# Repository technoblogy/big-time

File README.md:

# Big Time
A giant digital clock featuring four large LED displays.
For more information see: http://www.technoblogy.com/show?2WTD.

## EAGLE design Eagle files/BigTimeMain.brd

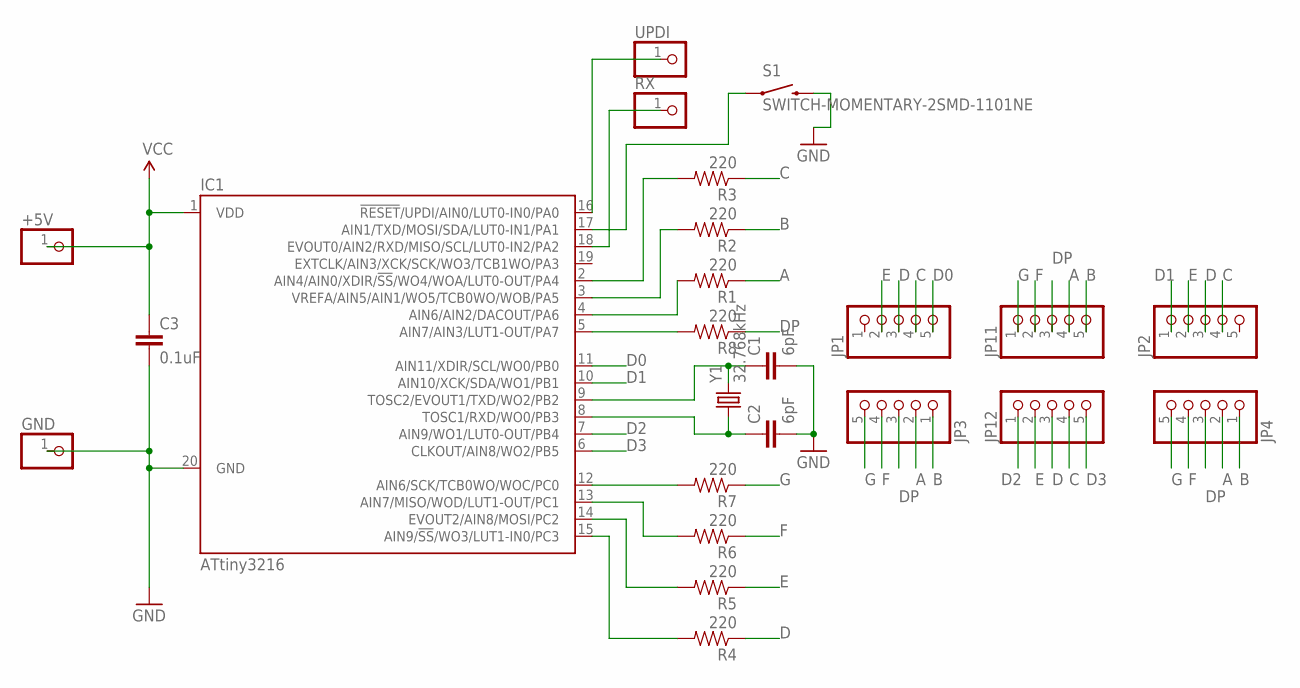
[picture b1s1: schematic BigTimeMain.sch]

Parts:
+5V: PINHD-1X1; 1X01
C1, C2: 6pF; 0805
C3: 0.1uF; 0805
GND: PINHD-1X1; 1X01
IC1: ATtiny3216; SOIC300
JP1, JP2, JP3, JP4, JP11, JP12: HEADER-1X576MIL; 1X05_ROUND_76
R1, R2, R3, R4, R5, R6, R7, R8: 220; 0805
RX: PINHD-1X1; 1X01
S1: SWITCH-MOMENTARY-2SMD-1101NE; TACTILE-SWITCH-1101NE
UPDI: PINHD-1X1; 1X01
Y1: 32.768kHz; CRYSTAL-SMD-3.2X1.5MM

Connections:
A: JP3.2, JP4.2, JP11.4, R1.1
B: JP3.1, JP4.1, JP11.5, R2.1
C: JP1.4, JP2.4, JP12.4, R3.1
D: JP1.3, JP2.3, JP12.3, R4.1
D0: IC1.11 (AIN11/XDIR/SCL/WO0/PB0), JP1.5
D1: IC1.10 (AIN10/XCK/SDA/WO1/PB1), JP2.1
D2: IC1.7 (AIN9/WO1/LUT0-OUT/PB4), JP12.1
D3: IC1.6 (CLKOUT/AIN8/WO2/PB5), JP12.5
DP: JP3.3, JP4.3, JP11.3, R8.1
E: JP1.2, JP2.2, JP12.2, R5.1
F: JP3.4, JP4.4, JP11.2, R6.1
G: JP3.5, JP4.5, JP11.1, R7.1
GND: C1.2, C2.2, C3.2, GND.1, IC1.20 (GND), S1.2
unnamed: C1.1, IC1.9 (TOSC2/EVOUT1/TXD/WO2/PB2), Y1.P$2 (2)
unnamed: C2.1, IC1.8 (TOSC1/RXD/WO0/PB3), Y1.P$1 (1)
unnamed: IC1.16 (!RESET!/UPDI/AIN0/LUT0-IN0/PA0), UPDI.1
unnamed: IC1.4 (AIN6/AIN2/DACOUT/PA6), R1.2
unnamed: IC1.3 (VREFA/AIN5/AIN1/WO5/TCB0WO/WOB/PA5), R2.2
unnamed: IC1.2 (AIN4/AIN0/XDIR/!SS!/WO4/WOA/LUT0-OUT/PA4), R3.2
unnamed: IC1.15 (AIN9/!SS!/WO3/LUT1-IN0/PC3), R4.2
unnamed: IC1.14 (EVOUT2/AIN8/MOSI/PC2), R5.2
unnamed: IC1.18 (EVOUT0/AIN2/RXD/MISO/SCL/LUT0-IN2/PA2), RX.1
unnamed: IC1.13 (AIN7/MISO/WOD/LUT1-OUT/PC1), R6.2
unnamed: IC1.12 (AIN6/SCK/TCB0WO/WOC/PC0), R7.2
unnamed: IC1.5 (AIN7/AIN3/LUT1-OUT/PA7), R8.2
unnamed: IC1.17 (AIN1/TXD/MOSI/SDA/LUT0-IN1/PA1), S1.1
VCC: +5V.1, C3.1, IC1.1 (VDD)

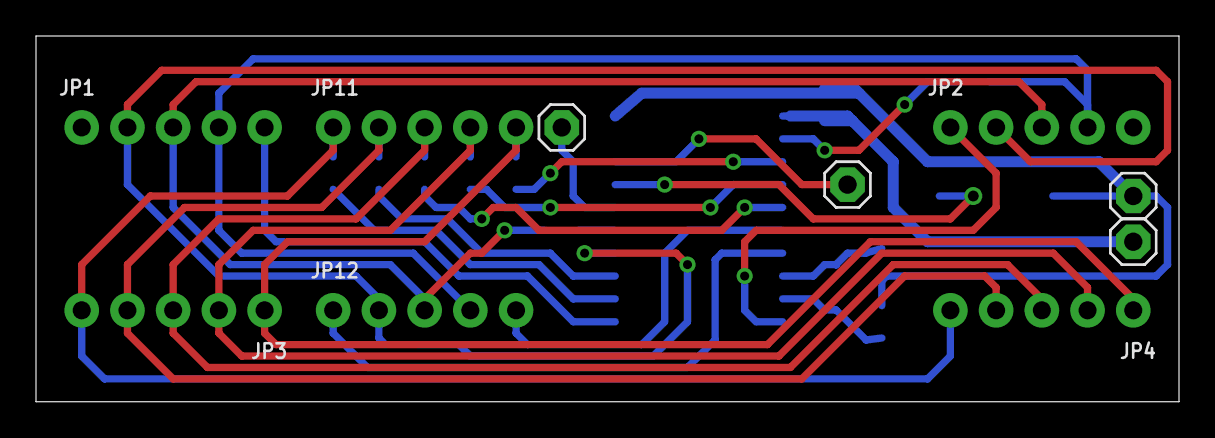
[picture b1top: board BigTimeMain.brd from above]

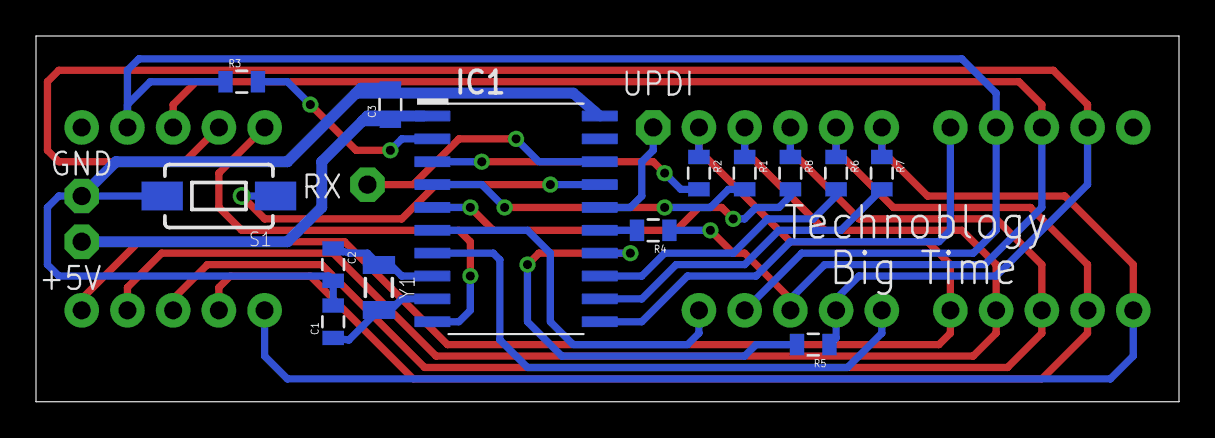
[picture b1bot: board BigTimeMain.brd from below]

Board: 2 copper layers, 63.5 x 20.3 mm, 24 parts (14 on the bottom side), 27 nets.

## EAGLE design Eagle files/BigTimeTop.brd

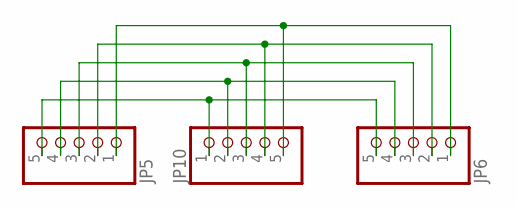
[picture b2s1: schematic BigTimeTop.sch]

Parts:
JP5, JP6, JP10: HEADER-1X576MIL; 1X05_ROUND_76

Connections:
unnamed: JP5.5, JP6.5, JP10.1
unnamed: JP5.4, JP6.4, JP10.2
unnamed: JP5.3, JP6.3, JP10.3
unnamed: JP5.2, JP6.2, JP10.4
unnamed: JP5.1, JP6.1, JP10.5

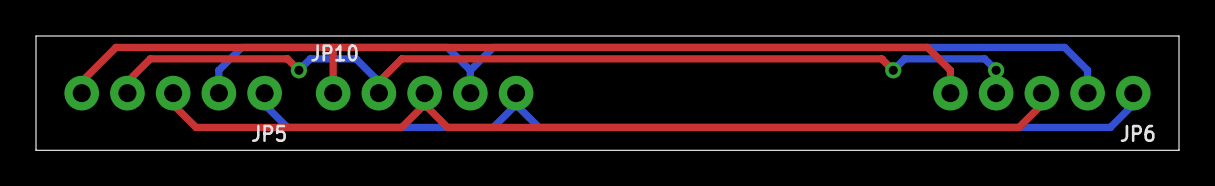
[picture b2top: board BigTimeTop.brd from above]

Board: 2 copper layers, 63.5 x 6.4 mm, 3 parts (0 on the bottom side), 5 nets.

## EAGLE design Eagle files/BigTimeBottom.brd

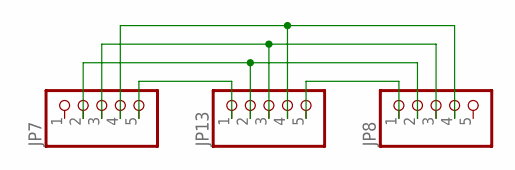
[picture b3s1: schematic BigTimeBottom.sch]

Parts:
JP7, JP8, JP13: HEADER-1X576MIL; 1X05_ROUND_76

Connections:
unnamed: JP7.5, JP13.1
unnamed: JP8.1, JP13.5
unnamed: JP7.2, JP8.2, JP13.2
unnamed: JP7.4, JP8.4, JP13.4
W1: JP7.3, JP8.3, JP13.3

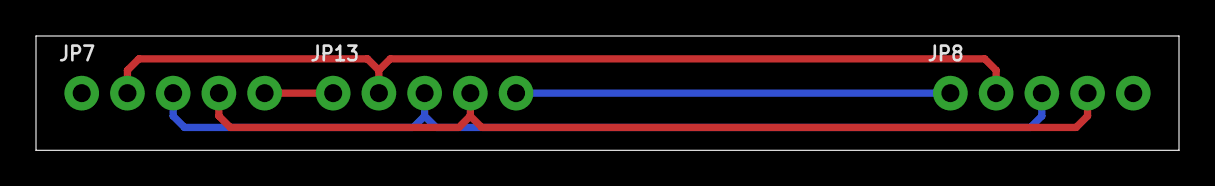
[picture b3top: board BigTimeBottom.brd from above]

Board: 2 copper layers, 63.5 x 6.3 mm, 3 parts (0 on the bottom side), 5 nets.

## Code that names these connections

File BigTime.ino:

/* Big Time Clock v2

   David Johnson-Davies - www.technoblogy.com - 28th January 2025
   ATtiny3216 @ 5 MHz (internal oscillator; BOD disabled)
   
   CC BY 4.0
   Licensed under a Creative Commons Attribution 4.0 International license: 
   http://creativecommons.org/licenses/by/4.0/
*/

#define TWELVEHOUR                    // Comment out for 24-hour clock

// Seven segment displays

const int charArrayLen = 12;
uint8_t charArray[charArrayLen] = {
//  abcdefg  Segments
  0b1111110, // 0
  0b0110000, // 1
  0b1101101, // 2
  0b1111001, // 3
  0b0110011, // 4
  0b1011011, // 5
  0b1011111, // 6
  0b1110000, // 7
  0b1111111, // 8
  0b1111011, // 9
  0b0000000, // 10  Space
  0b0000001  // 11  '-'
};

const int Space = 10;
const int Dash = 11;

// Display multiplexer **********************************************

const int Ndigits = 4;
uint8_t Digits[Ndigits] = { Dash, Dash, Dash, Dash };
uint8_t Pins[Ndigits] = { 0, 1, 4, 5};                // Port B output for each digit
int Digit = 0;

void DisplaySetup () {
  // Segment drivers
  PORTA.DIR = PIN4_bm | PIN5_bm | PIN6_bm | PIN7_bm;  // Set PA4-PA7 as outputs
  PORTC.DIR = PIN0_bm | PIN1_bm | PIN2_bm | PIN3_bm;  // Set PC0-PC3 as outputs
  // Digit drivers
  PORTB.DIR = PIN0_bm | PIN1_bm | PIN4_bm | PIN5_bm;  // Set PB0 PB1 PB4 PB5 outputs
  PORTB.OUT = PIN0_bm | PIN1_bm | PIN4_bm | PIN5_bm;  // Set PB0 PB1 PB4 PB5 high
  // Set up Timer/Counter TCB to multiplex the display
  TCB0.CCMP = 19999;                                  // Divide 5MHz by 20000 = 250Hz
  TCB0.CTRLA = TCB_CLKSEL_CLKDIV1_gc | TCB_ENABLE_bm; // Enable timer, divide by 1
  TCB0.CTRLB = 0;                                     // Periodic Interrupt Mode
  TCB0.INTCTRL = TCB_CAPT_bm;                         // Enable interrupt
}

// Timer/Counter TCB interrupt - multiplexes the display
ISR(TCB0_INT_vect) {
  TCB0.INTFLAGS = TCB_CAPT_bm;                        // Clear the interrupt flag
  DisplayNextDigit();
}
  
void DisplayNextDigit() {
  PORTB.OUTSET = 1<<Pins[Digit];                      // Take digit high
  Digit = (Digit+1) % Ndigits;
  uint8_t segs = charArray[Digits[Digit]];
  PORTA.OUT = segs & 0xF0;                            // Set PA4-PA7
  PORTC.OUT = segs & 0x0F;                            // Set PC0-PC3
  PORTB.OUTCLR = 1<<Pins[Digit];                      // Take digit low
}

// Set time button **********************************************

int ButtonState = 0;

void ButtonSetup () {
  PORTA.PIN1CTRL = PORT_PULLUPEN_bm;                  // PA1 input pullup
}

boolean ButtonDown () {
  return (PORTA.IN & PIN1_bm) == 0;                   // True if button pressed
}

// Real-Time Clock **********************************************

volatile unsigned long Time = 0;                      // In half seconds

void RTCSetup () {
  uint8_t temp;
  // Initialize 32.768kHz Oscillator:

  // Disable oscillator:
  temp = CLKCTRL.XOSC32KCTRLA & ~CLKCTRL_ENABLE_bm;

  // Enable writing to protected register
  CPU_CCP = CCP_IOREG_gc;
  CLKCTRL.XOSC32KCTRLA = temp;

  while (CLKCTRL.MCLKSTATUS & CLKCTRL_XOSC32KS_bm);   // Wait until XOSC32KS is 0
  
  temp = CLKCTRL.XOSC32KCTRLA & ~CLKCTRL_SEL_bm;      // Use External Crystal
  
  // Enable writing to protected register
  CPU_CCP = CCP_IOREG_gc;
  CLKCTRL.XOSC32KCTRLA = temp;
  
  temp = CLKCTRL.XOSC32KCTRLA | CLKCTRL_ENABLE_bm;    // Enable oscillator
  
  // Enable writing to protected register
  CPU_CCP = CCP_IOREG_gc;
  CLKCTRL.XOSC32KCTRLA = temp;
  
  // Initialize RTC
  while (RTC.STATUS > 0);                             // Wait until registers synchronized

  // 32.768kHz External Crystal Oscillator (XOSC32K)
  RTC.CLKSEL = RTC_CLKSEL_TOSC32K_gc;
  
  RTC.DBGCTRL = RTC_DBGRUN_bm; // Run in debug: enabled

  RTC.PITINTCTRL = RTC_PI_bm;                         // Periodic Interrupt: enabled
  
  // RTC Clock Cycles 16384, enabled ie 2Hz interrupt
  RTC.PITCTRLA = RTC_PERIOD_CYC16384_gc | RTC_PITEN_bm;
}

// Interrupt Service Routine called twice a second
ISR(RTC_PIT_vect) {
  int minutes, hours;
  RTC.PITINTFLAGS = RTC_PI_bm;                        // Clear interrupt flag
  minutes = (Time / 120) % 60;
#ifdef TWELVEHOUR
  hours = (Time / 7200) % 12;
#else
  hours = (Time / 7200) % 24;
#endif
  if (ButtonDown()) {
    if (ButtonState == 1 || ButtonState == 3) {
        ButtonState = (ButtonState + 1) % 4;
    }
    if (ButtonState == 0) {                           // Advance hours
#ifdef TWELVEHOUR
      hours = (hours + 1) % 12;
#else
      hours = (hours + 1) % 24;
#endif
    } else {                                          // Advance minutes
      minutes = (minutes + 1) % 60;
    }
    Time = (unsigned long)hours * 7200 + minutes * 120;
  } else {                                            // Button up
     if (ButtonState == 0 || ButtonState == 2) {
        ButtonState = (ButtonState + 1) % 4;
     }
     Time = (Time + 1) % 172800;                       // Wrap around after 24 hours
  }
#ifdef TWELVEHOUR
  hours = hours + 1;
#endif
  Digits[0] = hours/10;
  Digits[1] = hours%10;
  Digits[2] = minutes/10;
  Digits[3] = minutes%10;              
}

// Setup **********************************************

void setup () {
  DisplaySetup();
  RTCSetup();
  ButtonSetup();
}

// Everything done under interrupt
void loop () {
}

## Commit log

2020-01-28 Version 1 - 28th January 2020
2025-01-28 Version 2 - 28th January 2025
    Minor fix.

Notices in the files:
parts and their libraries:
microbuilder: This work is placed in the public domain, and may be freely used for commercial and non-commercial work with the following conditions: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
SparkFun-Resistors: Licensing: CC v3.0 Share-Alike You are welcome to use this library for commercial purposes.
